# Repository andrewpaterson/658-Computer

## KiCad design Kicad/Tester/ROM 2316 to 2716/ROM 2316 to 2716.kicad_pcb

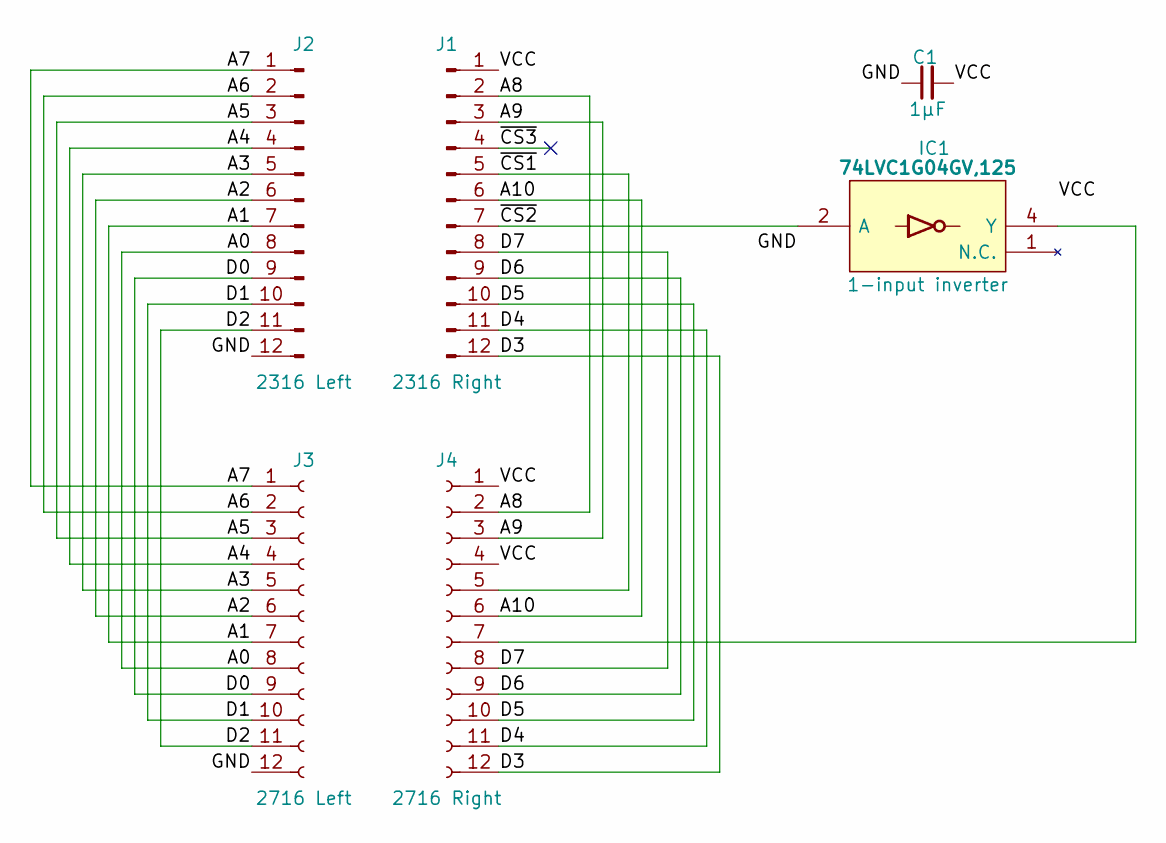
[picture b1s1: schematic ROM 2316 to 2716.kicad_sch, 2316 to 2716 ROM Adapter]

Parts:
C1: 1μF; C_0805
IC1: 74LVC1G04GV,125; SOT95P275X110-5N; Manufacturer_Part_Number 74LVC1G04GV,125; Mouser Part Number 771-74LVC1G04GV
J1: 2316 Right; Pin_1x12_P2.54mm_Vertical
J2: 2316 Left; Pin_1x12_P2.54mm_Vertical
J3: 2716 Left; Pin_1x12_P2.54mm_Vertical
J4: 2716 Right; Pin_1x12_P2.54mm_Vertical

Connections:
/A0: J2.8, J3.8
/A1: J2.7, J3.7
/A2: J2.6, J3.6
/A3: J2.5, J3.5
/A4: J2.4, J3.4
/A5: J2.3, J3.3
/A6: J2.2, J3.2
/A7: J2.1, J3.1
/A8: J1.2, J4.2
/A9: J1.3, J4.3
/A10: J1.6, J4.6
/D0: J2.9, J3.9
/D1: J2.10, J3.10
/D2: J2.11, J3.11
/D3: J1.12, J4.12
/D4: J1.11, J4.11
/D5: J1.10, J4.10
/D6: J1.9, J4.9
/D7: J1.8, J4.8
/GND: C1.1, IC1.3 (GND), J2.12, J3.12
/VCC: C1.2, IC1.5 (3V), J1.1, J4.1, J4.4
/~CS1: J1.5, J4.5
/~CS2: IC1.2 (A), J1.7
/~CS3: J1.4
unnamed: IC1.4 (Y), J4.7

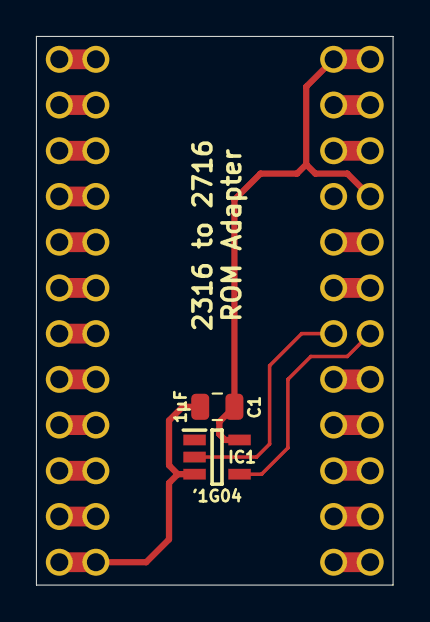
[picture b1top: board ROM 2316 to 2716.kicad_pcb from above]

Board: 2 copper layers, 19.8 x 30.5 mm, 6 parts (0 on the bottom side), 24 nets.

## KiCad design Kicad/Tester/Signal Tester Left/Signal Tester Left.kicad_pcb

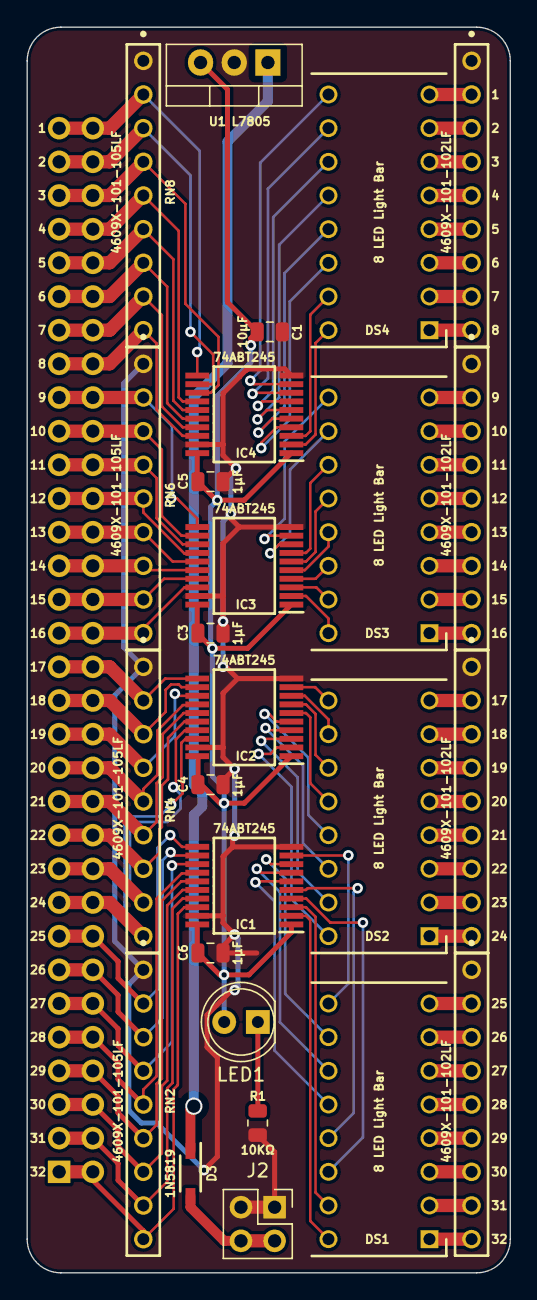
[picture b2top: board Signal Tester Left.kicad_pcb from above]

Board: 2 copper layers, 36.4 x 94.0 mm, 27 parts (1 on the bottom side), 101 nets.

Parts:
C1: 10µF; C_0805
C3, C4, C5, C6: 1μF; C_0805
D3: 1N5819HW-7-F; SOD3716X145N
DS1, DS2, DS3, DS4: 8 LED Light Bar; DIP8LEDBAR
IC1, IC2, IC3, IC4: SN74ABT245BDBR; SOP65P780X200-20N
J2: Conn_02x02_Odd_Even; PinSocket_2x02_P2.54mm_Vertical
J3: Conn_02x32_Odd_Even; PinHeader_2x32_P2.54mm_Vertical
LED1: LED_Small_Filled; LED_D5.0mm
R1: 10KΩ; R_0805
RN1, RN3, RN5, RN7: 4609X-101-102LF; 4609X
RN2, RN4, RN6, RN8: 4609X-101-105LF; 4609X
U1: L7805; TO-220-3_Vertical

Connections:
/5V: C1.1, C3.2, C4.2, C5.2, C6.2, IC1.1 (DIR), IC1.20 (5V), IC2.1 (DIR), IC2.20 (5V), IC3.1 (DIR), IC3.20 (5V), IC4.1 (DIR), IC4.20 (5V), LED1.2 (A), U1.3 (OUT)
/12V Forward: D3.1, U1.1 (IN)
/D0: IC1.18 (B0), J3.1, J3.2, RN2.9 (R8)
/D1: IC1.17 (B1), J3.3, J3.4, RN2.8 (R7)
/D2: IC1.16 (B2), J3.5, J3.6, RN2.7 (R6)
/D3: IC1.15 (B3), J3.7, J3.8, RN2.6 (R5)
/D4: IC1.14 (B4), J3.9, J3.10, RN2.5 (R4)
/D5: IC1.13 (B5), J3.11, J3.12, RN2.4 (R3)
/D6: IC1.12 (B6), J3.13, J3.14, RN2.3 (R2)
/D7: IC1.11 (B7), J3.15, J3.16, RN2.2 (R1)
/D8: IC2.18 (B0), J3.17, J3.18, RN4.9 (R8)
/D9: IC2.17 (B1), J3.19, J3.20, RN4.8 (R7)
/D10: IC2.16 (B2), J3.21, J3.22, RN4.7 (R6)
/D11: IC2.15 (B3), J3.23, J3.24, RN4.6 (R5)
/D12: IC2.14 (B4), J3.25, J3.26, RN4.5 (R4)
/D13: IC2.13 (B5), J3.27, J3.28, RN4.4 (R3)
/D14: IC2.12 (B6), J3.29, J3.30, RN4.3 (R2)
/D15: IC2.11 (B7), J3.31, J3.32, RN4.2 (R1)
/D16: IC3.18 (B0), J3.33, J3.34, RN6.9 (R8)
/D17: IC3.17 (B1), J3.35, J3.36, RN6.8 (R7)
/D18: IC3.16 (B2), J3.37, J3.38, RN6.7 (R6)
/D19: IC3.15 (B3), J3.39, J3.40, RN6.6 (R5)
/D20: IC3.14 (B4), J3.41, J3.42, RN6.5 (R4)
/D21: IC3.13 (B5), J3.43, J3.44, RN6.4 (R3)
/D22: IC3.12 (B6), J3.45, J3.46, RN6.3 (R2)
/D23: IC3.11 (B7), J3.47, J3.48, RN6.2 (R1)
/D24: IC4.18 (B0), J3.49, J3.50, RN8.9 (R8)
/D25: IC4.17 (B1), J3.51, J3.52, RN8.8 (R7)
/D26: IC4.16 (B2), J3.53, J3.54, RN8.7 (R6)
/D27: IC4.15 (B3), J3.55, J3.56, RN8.6 (R5)
/D28: IC4.14 (B4), J3.57, J3.58, RN8.5 (R4)
/D29: IC4.13 (B5), J3.59, J3.60, RN8.4 (R3)
/D30: IC4.12 (B6), J3.61, J3.62, RN8.3 (R2)
/D31: IC4.11 (B7), J3.63, J3.64, RN8.2 (R1)
/GND: C1.2, C3.1, C4.1, C5.1, C6.1, IC1.10 (GND), IC1.19 (~OE), IC2.10 (GND), IC2.19 (~OE), IC3.10 (GND), IC3.19 (~OE), IC4.10 (GND), IC4.19 (~OE), J2.1, J2.2, R1.1, RN1.1 (PC), RN2.1 (PC), RN3.1 (PC), RN4.1 (PC), RN5.1 (PC), RN6.1 (PC), RN7.1 (PC), RN8.1 (PC), U1.2 (GND)
unnamed: DS1.1 (ANODE_A), RN1.9 (R8)
unnamed: DS1.2 (ANODE_B), RN1.8 (R7)
unnamed: DS1.3 (ANODE_C), RN1.7 (R6)
unnamed: DS1.4 (ANODE_D), RN1.6 (R5)
unnamed: DS1.5 (ANODE_E), RN1.5 (R4)
unnamed: DS1.6 (ANODE_F), RN1.4 (R3)
unnamed: DS1.7 (ANODE_G), RN1.3 (R2)
unnamed: DS1.8 (ANODE_H), RN1.2 (R1)
unnamed: DS1.16 (CATHODE_A), IC1.2 (A0)
unnamed: DS1.15 (CATHODE_B), IC1.3 (A1)
unnamed: DS1.14 (CATHODE_C), IC1.4 (A2)
unnamed: DS1.13 (CATHODE_D), IC1.5 (A3)
unnamed: DS1.12 (CATHODE_E), IC1.6 (A4)
unnamed: DS1.11 (CATHODE_F), IC1.7 (A5)
unnamed: DS1.10 (CATHODE_G), IC1.8 (A6)
unnamed: DS1.9 (CATHODE_H), IC1.9 (A7)
unnamed: DS2.1 (ANODE_A), RN3.9 (R8)
unnamed: DS2.2 (ANODE_B), RN3.8 (R7)
unnamed: DS2.3 (ANODE_C), RN3.7 (R6)
unnamed: DS2.4 (ANODE_D), RN3.6 (R5)
unnamed: DS2.5 (ANODE_E), RN3.5 (R4)
unnamed: DS2.6 (ANODE_F), RN3.4 (R3)
unnamed: DS2.7 (ANODE_G), RN3.3 (R2)
unnamed: DS2.8 (ANODE_H), RN3.2 (R1)
unnamed: DS2.16 (CATHODE_A), IC2.2 (A0)
unnamed: DS2.15 (CATHODE_B), IC2.3 (A1)
unnamed: DS2.14 (CATHODE_C), IC2.4 (A2)
unnamed: DS2.13 (CATHODE_D), IC2.5 (A3)
unnamed: DS2.12 (CATHODE_E), IC2.6 (A4)
unnamed: DS2.11 (CATHODE_F), IC2.7 (A5)
unnamed: DS2.10 (CATHODE_G), IC2.8 (A6)
unnamed: DS2.9 (CATHODE_H), IC2.9 (A7)
unnamed: DS3.1 (ANODE_A), RN5.9 (R8)
unnamed: DS3.2 (ANODE_B), RN5.8 (R7)
unnamed: DS3.3 (ANODE_C), RN5.7 (R6)
unnamed: DS3.4 (ANODE_D), RN5.6 (R5)
unnamed: DS3.5 (ANODE_E), RN5.5 (R4)
unnamed: DS3.6 (ANODE_F), RN5.4 (R3)
unnamed: DS3.7 (ANODE_G), RN5.3 (R2)
unnamed: DS3.8 (ANODE_H), RN5.2 (R1)
unnamed: DS3.16 (CATHODE_A), IC3.2 (A0)
unnamed: DS3.15 (CATHODE_B), IC3.3 (A1)
unnamed: DS3.14 (CATHODE_C), IC3.4 (A2)
unnamed: DS3.13 (CATHODE_D), IC3.5 (A3)
unnamed: DS3.12 (CATHODE_E), IC3.6 (A4)
unnamed: DS3.11 (CATHODE_F), IC3.7 (A5)
unnamed: DS3.10 (CATHODE_G), IC3.8 (A6)
unnamed: DS3.9 (CATHODE_H), IC3.9 (A7)
unnamed: DS4.1 (ANODE_A), RN7.9 (R8)
unnamed: DS4.2 (ANODE_B), RN7.8 (R7)
unnamed: DS4.3 (ANODE_C), RN7.7 (R6)
unnamed: DS4.4 (ANODE_D), RN7.6 (R5)
unnamed: DS4.5 (ANODE_E), RN7.5 (R4)
unnamed: DS4.6 (ANODE_F), RN7.4 (R3)
unnamed: DS4.7 (ANODE_G), RN7.3 (R2)
unnamed: DS4.8 (ANODE_H), RN7.2 (R1)
unnamed: DS4.16 (CATHODE_A), IC4.2 (A0)
unnamed: DS4.15 (CATHODE_B), IC4.3 (A1)
unnamed: DS4.14 (CATHODE_C), IC4.4 (A2)
unnamed: DS4.13 (CATHODE_D), IC4.5 (A3)
unnamed: DS4.12 (CATHODE_E), IC4.6 (A4)
unnamed: DS4.11 (CATHODE_F), IC4.7 (A5)
unnamed: DS4.10 (CATHODE_G), IC4.8 (A6)
unnamed: DS4.9 (CATHODE_H), IC4.9 (A7)
unnamed: D3.2, J2.3, J2.4
unnamed: LED1.1 (K), R1.2

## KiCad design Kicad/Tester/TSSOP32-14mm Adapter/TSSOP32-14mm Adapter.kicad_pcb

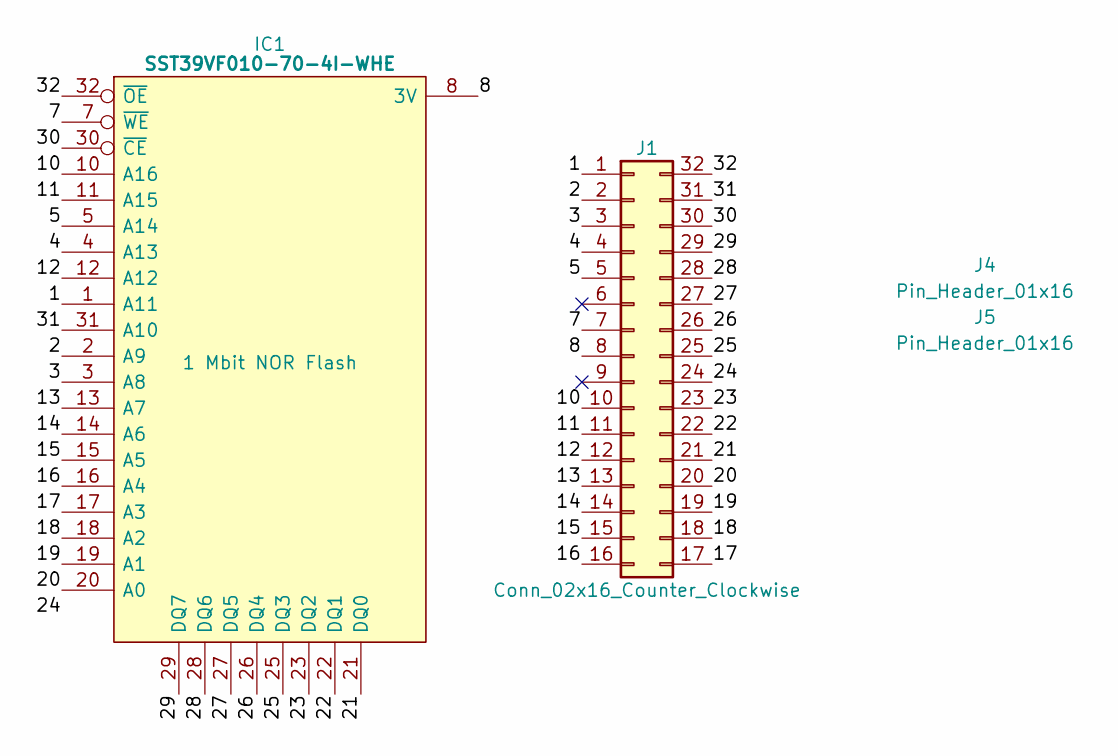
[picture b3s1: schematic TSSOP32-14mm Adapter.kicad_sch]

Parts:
IC1: SST39VF010-70-4I-WHE; SOP50P1400X120-32N; Manufacturer_Part_Number SST39VF010-70-4I-WHE-T; Mouser Part Number 579-39VF0107IWHET
J1: Conn_02x16_Counter_Clockwise; DIP-32_W15.24mm_Socket
J4, J5: Pin_Header_01x16; PinHeader_1x16_P2.54mm_Vertical

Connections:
/1: IC1.1 (A11), J1.1
/2: IC1.2 (A9), J1.2
/3: IC1.3 (A8), J1.3
/4: IC1.4 (A13), J1.4
/5: IC1.5 (A14), J1.5
/7: IC1.7 (~WE), J1.7
/8: IC1.8 (3V), J1.8
/10: IC1.10 (A16), J1.10
/11: IC1.11 (A15), J1.11
/12: IC1.12 (A12), J1.12
/13: IC1.13 (A7), J1.13
/14: IC1.14 (A6), J1.14
/15: IC1.15 (A5), J1.15
/16: IC1.16 (A4), J1.16
/17: IC1.17 (A3), J1.17
/18: IC1.18 (A2), J1.18
/19: IC1.19 (A1), J1.19
/20: IC1.20 (A0), J1.20
/21: IC1.21 (DQ0), J1.21
/22: IC1.22 (DQ1), J1.22
/23: IC1.23 (DQ2), J1.23
/24: IC1.24 (GND), J1.24
/25: IC1.25 (DQ3), J1.25
/26: IC1.26 (DQ4), J1.26
/27: IC1.27 (DQ5), J1.27
/28: IC1.28 (DQ6), J1.28
/29: IC1.29 (DQ7), J1.29
/30: IC1.30 (~CE), J1.30
/31: IC1.31 (A10), J1.31
/32: IC1.32 (~OE), J1.32

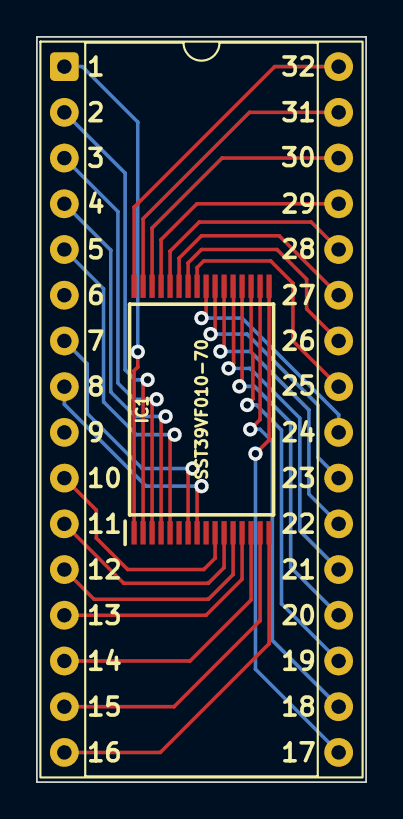
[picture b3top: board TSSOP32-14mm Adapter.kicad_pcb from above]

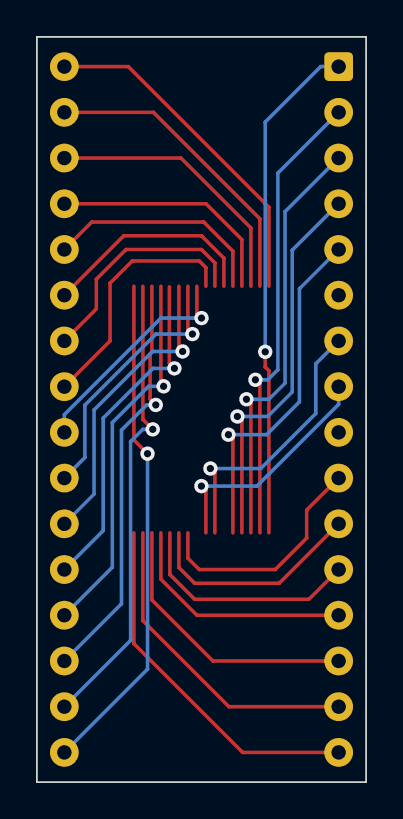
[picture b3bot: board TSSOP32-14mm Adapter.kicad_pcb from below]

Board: 2 copper layers, 18.3 x 41.4 mm, 4 parts (2 on the bottom side), 30 nets.

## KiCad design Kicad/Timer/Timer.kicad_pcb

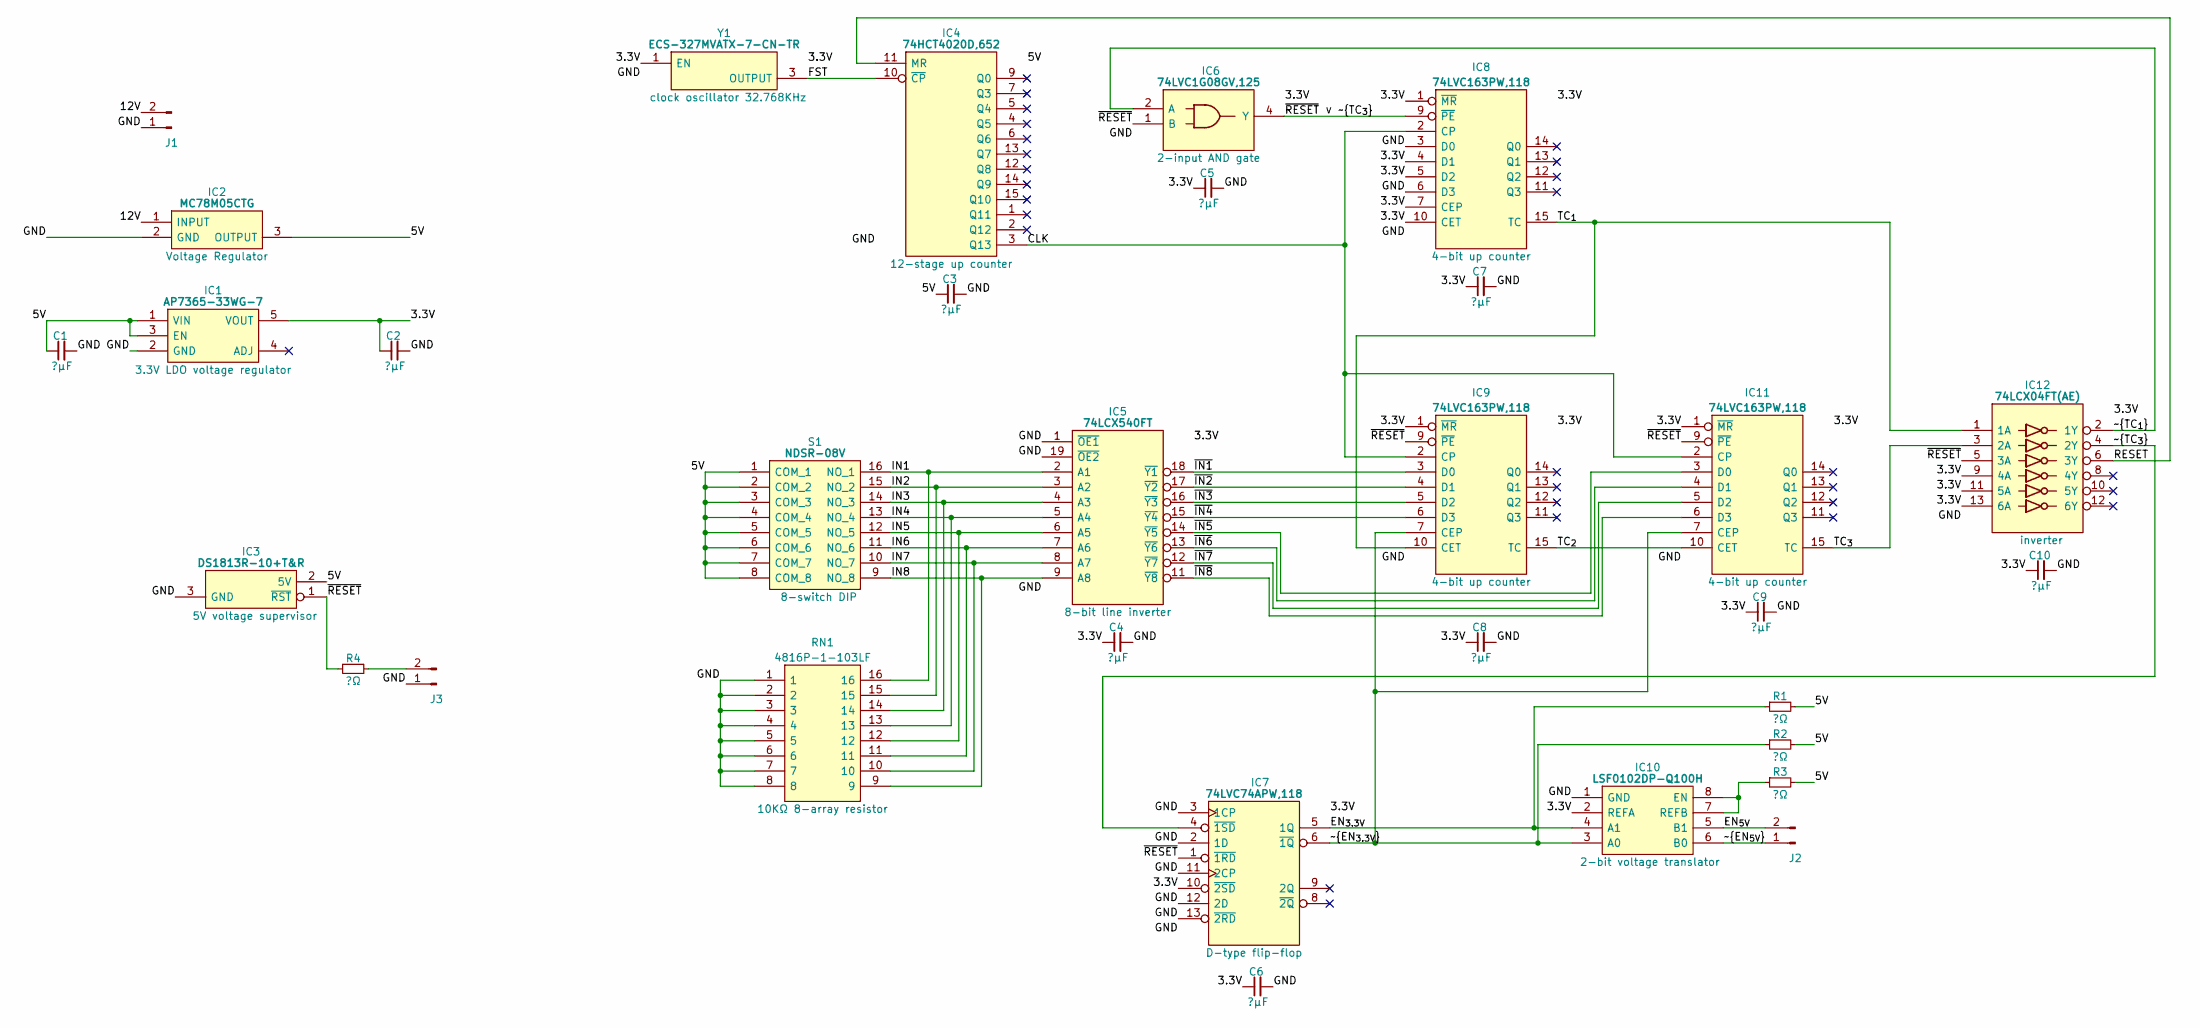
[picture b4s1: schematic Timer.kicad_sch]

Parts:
C1, C2, C3, C4, C5, C6, C7, C8, C9, C10: C_0805
IC1: AP7365-33WG-7; SOT95P285X130-5N; Manufacturer_Part_Number AP7365-33WG-7; Mouser Part Number 621-AP7365-33WG-7
IC2: MC78M05CTG; TO254P482X997X2018-3P; Manufacturer_Part_Number MC78M05CTG; Mouser Part Number 863-MC78M05CTG
IC3: DS1813R-10+T&R; SOT95P237X112-3N; Mouser Part Number 700-DS1813R-10T&R
IC4: 74HCT4020D,652; 74HCT4020D652; Manufacturer_Part_Number 74HCT4020D,652; Mouser Part Number 771-74HCT4020D
IC5: 74LCX540FT; SOP65P640X120-20N; Manufacturer_Part_Number 74LCX540FT; Mouser Part Number 757-74LCX540FT
IC6: 74LVC1G08GV,125; SOT95P275X110-5N; Manufacturer_Part_Number 74LVC1G08GV,125; Mouser Part Number 771-74LVC1G08GV
IC7: 74LVC74APW,118; SOP65P640X110-14N; Mouser Part Number 771-74LVC74APW-T
IC8, IC9, IC11: 74LVC163PW,118; SOP65P640X110-16N; Mouser Part Number 771-74LVC163PW-T
IC10: LSF0102DP-Q100H; SOP65P400X110-8N; Manufacturer_Part_Number LSF0102DP-Q100H; Mouser Part Number 771-LSF0102DP-Q100H
IC12: 74LCX04FT(AE); SOP65P640X120-14N; Mouser Part Number 757-74LCX04FTAE
J1, J2, J3: Conn_01x02_Male
R1, R2, R3, R4: R_0805
RN1: 4816P-1-103LF; SOIC127P762X240-16N; Manufacturer_Part_Number 4816P-1-103LF; Mouser Part Number 652-4816P-1LF-10K
S1: NDSR-08V; DIPS762W77P254L2168H585Q16N; Manufacturer_Part_Number NDSR-08-V
Y1: ECS-327MVATX-7-CN-TR; ECS327MVATX7CNTR; Manufacturer_Part_Number ECS-327MVATX-7-CN-TR; Mouser Part Number 520-327MVATX-7-CNT

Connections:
/3.3V: C2.1, C4.1, C5.1, C6.1, C7.1, C8.1, C9.1, C10.1, IC1.5 (VOUT), IC5.20 (3V), IC6.5 (3V), IC7.10 (~2SD), IC7.14 (3V), IC8.1 (~MR), IC8.4 (D1), IC8.5 (D2), IC8.7 (CEP), IC8.10 (CET), IC8.16 (3V), IC9.1 (~MR), IC9.16 (3V), IC10.2 (REFA), IC11.1 (~MR), IC11.16 (3V), IC12.9 (4A), IC12.11 (5A), IC12.13 (6A), IC12.14 (3V), Y1.1 (EN), Y1.4 (3V)
/5V: C1.1, C3.1, IC1.1 (VIN), IC1.3 (EN), IC2.3 (OUTPUT), IC3.2 (5V), IC4.16 (5V), R1.2, R2.2, R3.2, S1.1 (COM_1), S1.2 (COM_2), S1.3 (COM_3), S1.4 (COM_4), S1.5 (COM_5), S1.6 (COM_6), S1.7 (COM_7), S1.8 (COM_8)
/12V: IC2.1 (INPUT), J1.2
/CLK: IC4.3 (Q13), IC8.2 (CP), IC9.2 (CP), IC11.2 (CP)
/EN_{3.3V}: IC7.5 (1Q), IC10.4 (A1), R1.1
/EN_{5V}: IC10.5 (B1), J2.2
/FST: IC4.10 (~CP), Y1.3 (OUTPUT)
/GND: C1.2, C2.2, C3.2, C4.2, C5.2, C6.2, C7.2, C8.2, C9.2, C10.2, IC1.2 (GND), IC2.2 (GND), IC3.3 (GND), IC4.8 (GND), IC5.1 (~OE1), IC5.10 (GND), IC5.19 (~OE2), IC6.3 (GND), IC7.2 (1D), IC7.3 (1CP), IC7.7 (GND), IC7.11 (2CP), IC7.12 (2D), IC7.13 (~2RD), IC8.3 (D0), IC8.6 (D3), IC8.8 (GND), IC9.8 (GND), IC10.1 (GND), IC11.8 (GND), IC12.7 (GND), J1.1, J3.1, RN1.1, RN1.2, RN1.3, RN1.4, RN1.5, RN1.6, RN1.7, RN1.8, Y1.2 (GND)
/IN1: IC5.2 (A1), RN1.16, S1.16 (NO_1)
/IN2: IC5.3 (A2), RN1.15, S1.15 (NO_2)
/IN3: IC5.4 (A3), RN1.14, S1.14 (NO_3)
/IN4: IC5.5 (A4), RN1.13, S1.13 (NO_4)
/IN5: IC5.6 (A5), RN1.12, S1.12 (NO_5)
/IN6: IC5.7 (A6), RN1.11, S1.11 (NO_6)
/IN7: IC5.8 (A7), RN1.10, S1.10 (NO_7)
/IN8: IC5.9 (A8), RN1.9, S1.9 (NO_8)
/RESET: IC4.11 (MR), IC12.6 (3Y)
/TC_{1}: IC8.15 (TC), IC9.10 (CET), IC12.1 (1A)
/TC_{2}: IC9.15 (TC), IC11.10 (CET)
/TC_{3}: IC11.15 (TC), IC12.3 (2A)
/~EN_{3.3V}: IC7.6 (~1Q), IC9.7 (CEP), IC10.3 (A0), IC11.7 (CEP), R2.1
/~EN_{5V}: IC10.6 (B0), J2.1
/~IN1: IC5.18 (~Y1), IC9.3 (D0)
/~IN2: IC5.17 (~Y2), IC9.4 (D1)
/~IN3: IC5.16 (~Y3), IC9.5 (D2)
/~IN4: IC5.15 (~Y4), IC9.6 (D3)
/~IN5: IC5.14 (~Y5), IC11.3 (D0)
/~IN6: IC5.13 (~Y6), IC11.4 (D1)
/~IN7: IC5.12 (~Y7), IC11.5 (D2)
/~IN8: IC5.11 (~Y8), IC11.6 (D3)
/~RESET: IC3.1 (~RST), IC6.1 (B), IC7.1 (~1RD), IC9.9 (~PE), IC11.9 (~PE), IC12.5 (3A), R4.1
/~RESET ∨ ~TC_{3}: IC6.4 (Y), IC8.9 (~PE)
/~TC_{1}: IC6.2 (A), IC12.2 (1Y)
/~TC_{3}: IC7.4 (~1SD), IC12.4 (2Y)
unnamed: IC10.7 (REFB), IC10.8 (EN), R3.1
unnamed: J3.2, R4.2

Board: 2 copper layers, 32 parts (0 on the bottom side), 36 nets, no tracks yet.

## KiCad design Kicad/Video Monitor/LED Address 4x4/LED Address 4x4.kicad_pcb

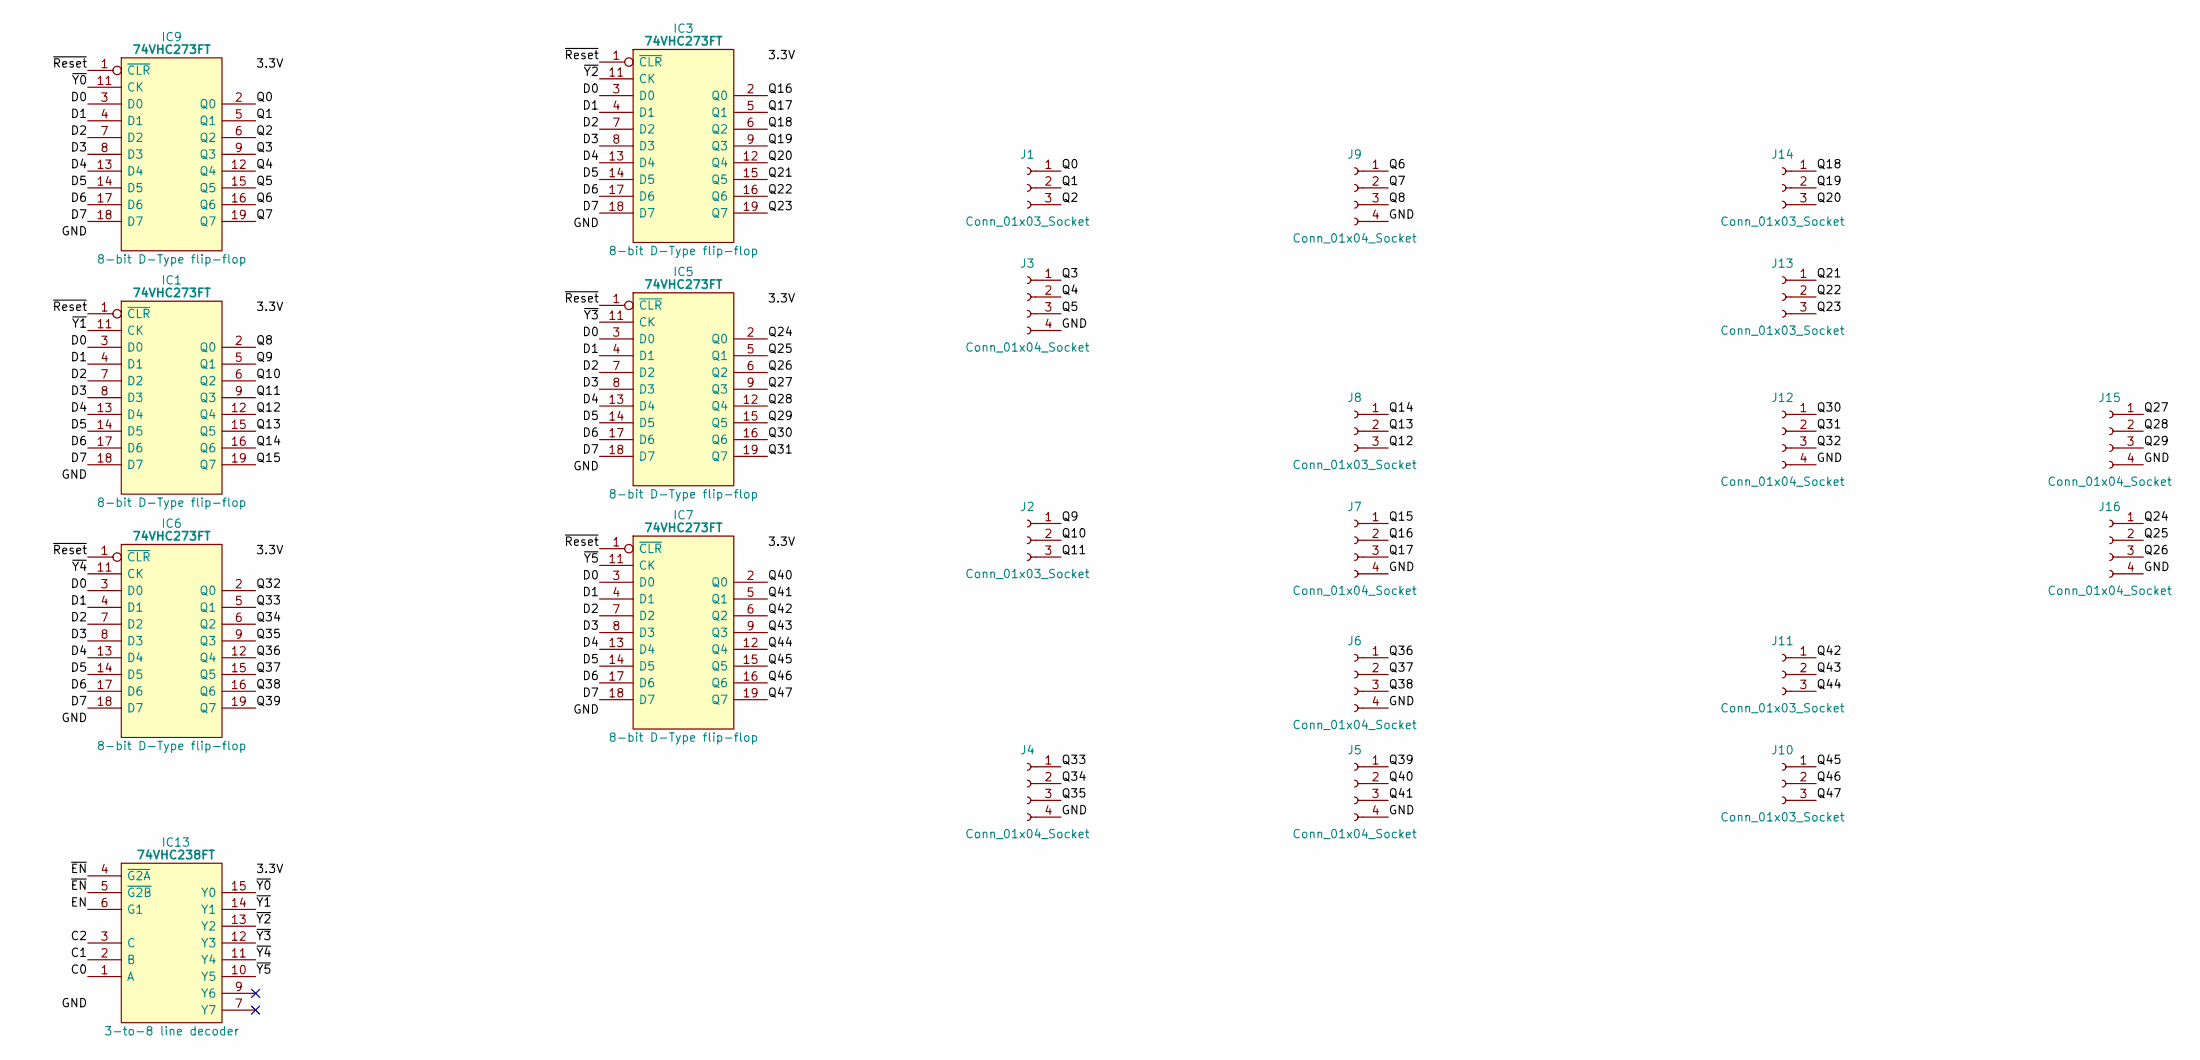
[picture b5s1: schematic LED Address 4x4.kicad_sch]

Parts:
IC1, IC3, IC5, IC6, IC7, IC9: 74VHC273FT; SOP65P640X110-20N; Manufacturer_Part_Number 74VHC273FT
IC13: 74VHC238FT; SOP65P640X120-16N; Mouser Part Number 757-74VHC238FT
J1, J2, J8, J10, J11, J13, J14: Conn_01x03_Socket; LED_Connector_3_SMD
J3, J4, J5, J6, J7, J9, J12, J15, J16: Conn_01x04_Socket; LED_Connector_4_SMD

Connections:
/3.3V: IC1.20 (5V), IC3.20 (5V), IC5.20 (5V), IC6.20 (5V), IC7.20 (5V), IC9.20 (5V), IC13.16 (5V)
/C0: IC13.1 (A)
/C1: IC13.2 (B)
/C2: IC13.3 (C)
/D0: IC1.3 (D0), IC3.3 (D0), IC5.3 (D0), IC6.3 (D0), IC7.3 (D0), IC9.3 (D0)
/D1: IC1.4 (D1), IC3.4 (D1), IC5.4 (D1), IC6.4 (D1), IC7.4 (D1), IC9.4 (D1)
/D2: IC1.7 (D2), IC3.7 (D2), IC5.7 (D2), IC6.7 (D2), IC7.7 (D2), IC9.7 (D2)
/D3: IC1.8 (D3), IC3.8 (D3), IC5.8 (D3), IC6.8 (D3), IC7.8 (D3), IC9.8 (D3)
/D4: IC1.13 (D4), IC3.13 (D4), IC5.13 (D4), IC6.13 (D4), IC7.13 (D4), IC9.13 (D4)
/D5: IC1.14 (D5), IC3.14 (D5), IC5.14 (D5), IC6.14 (D5), IC7.14 (D5), IC9.14 (D5)
/D6: IC1.17 (D6), IC3.17 (D6), IC5.17 (D6), IC6.17 (D6), IC7.17 (D6), IC9.17 (D6)
/D7: IC1.18 (D7), IC3.18 (D7), IC5.18 (D7), IC6.18 (D7), IC7.18 (D7), IC9.18 (D7)
/EN: IC13.6 (G1)
/GND: IC1.10 (GND), IC3.10 (GND), IC5.10 (GND), IC6.10 (GND), IC7.10 (GND), IC9.10 (GND), IC13.8 (GND), J3.4, J4.4, J5.4, J6.4, J7.4, J9.4, J12.4, J15.4, J16.4
/Q0: IC9.2 (Q0), J1.1
/Q1: IC9.5 (Q1), J1.2
/Q2: IC9.6 (Q2), J1.3
/Q3: IC9.9 (Q3), J3.1
/Q4: IC9.12 (Q4), J3.2
/Q5: IC9.15 (Q5), J3.3
/Q6: IC9.16 (Q6), J9.1
/Q7: IC9.19 (Q7), J9.2
/Q8: IC1.2 (Q0), J9.3
/Q9: IC1.5 (Q1), J2.1
/Q10: IC1.6 (Q2), J2.2
/Q11: IC1.9 (Q3), J2.3
/Q12: IC1.12 (Q4), J8.3
/Q13: IC1.15 (Q5), J8.2
/Q14: IC1.16 (Q6), J8.1
/Q15: IC1.19 (Q7), J7.1
/Q16: IC3.2 (Q0), J7.2
/Q17: IC3.5 (Q1), J7.3
/Q18: IC3.6 (Q2), J14.1
/Q19: IC3.9 (Q3), J14.2
/Q20: IC3.12 (Q4), J14.3
/Q21: IC3.15 (Q5), J13.1
/Q22: IC3.16 (Q6), J13.2
/Q23: IC3.19 (Q7), J13.3
/Q24: IC5.2 (Q0), J16.1
/Q25: IC5.5 (Q1), J16.2
/Q26: IC5.6 (Q2), J16.3
/Q27: IC5.9 (Q3), J15.1
/Q28: IC5.12 (Q4), J15.2
/Q29: IC5.15 (Q5), J15.3
/Q30: IC5.16 (Q6), J12.1
/Q31: IC5.19 (Q7), J12.2
/Q32: IC6.2 (Q0), J12.3
/Q33: IC6.5 (Q1), J4.1
/Q34: IC6.6 (Q2), J4.2
/Q35: IC6.9 (Q3), J4.3
/Q36: IC6.12 (Q4), J6.1
/Q37: IC6.15 (Q5), J6.2
/Q38: IC6.16 (Q6), J6.3
/Q39: IC6.19 (Q7), J5.1
/Q40: IC7.2 (Q0), J5.2
/Q41: IC7.5 (Q1), J5.3
/Q42: IC7.6 (Q2), J11.1
/Q43: IC7.9 (Q3), J11.2
/Q44: IC7.12 (Q4), J11.3
/Q45: IC7.15 (Q5), J10.1
/Q46: IC7.16 (Q6), J10.2
/Q47: IC7.19 (Q7), J10.3
/~EN: IC13.4 (~G2A), IC13.5 (~G2B)
/~Reset: IC1.1 (~CLR), IC3.1 (~CLR), IC5.1 (~CLR), IC6.1 (~CLR), IC7.1 (~CLR), IC9.1 (~CLR)
/~Y0: IC9.11 (CK), IC13.15 (Y0)
/~Y1: IC1.11 (CK), IC13.14 (Y1)
/~Y2: IC3.11 (CK), IC13.13 (Y2)
/~Y3: IC5.11 (CK), IC13.12 (Y3)
/~Y4: IC6.11 (CK), IC13.11 (Y4)
/~Y5: IC7.11 (CK), IC13.10 (Y5)

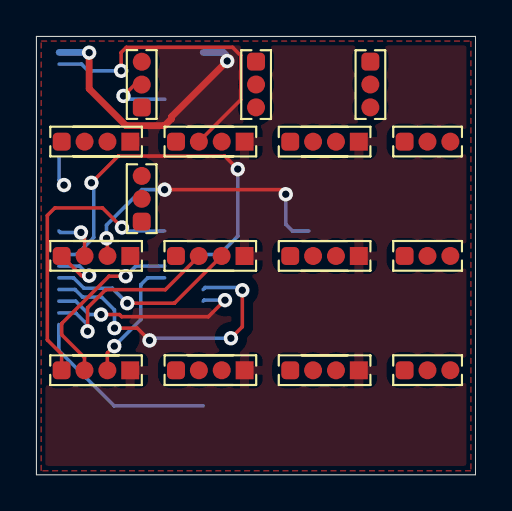
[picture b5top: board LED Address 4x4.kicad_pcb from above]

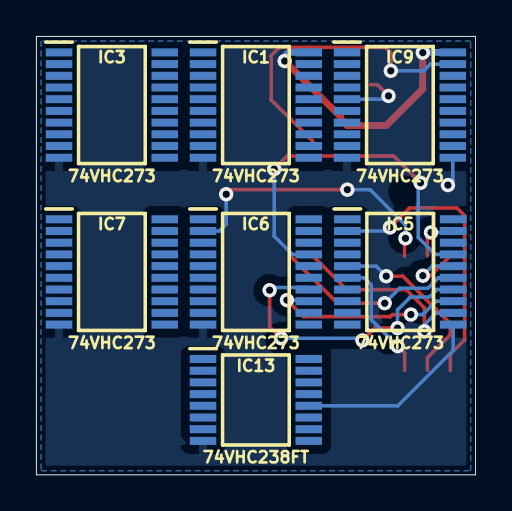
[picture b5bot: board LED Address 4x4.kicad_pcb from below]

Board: 2 copper layers, 24.4 x 24.4 mm, 23 parts (7 on the bottom side), 66 nets.

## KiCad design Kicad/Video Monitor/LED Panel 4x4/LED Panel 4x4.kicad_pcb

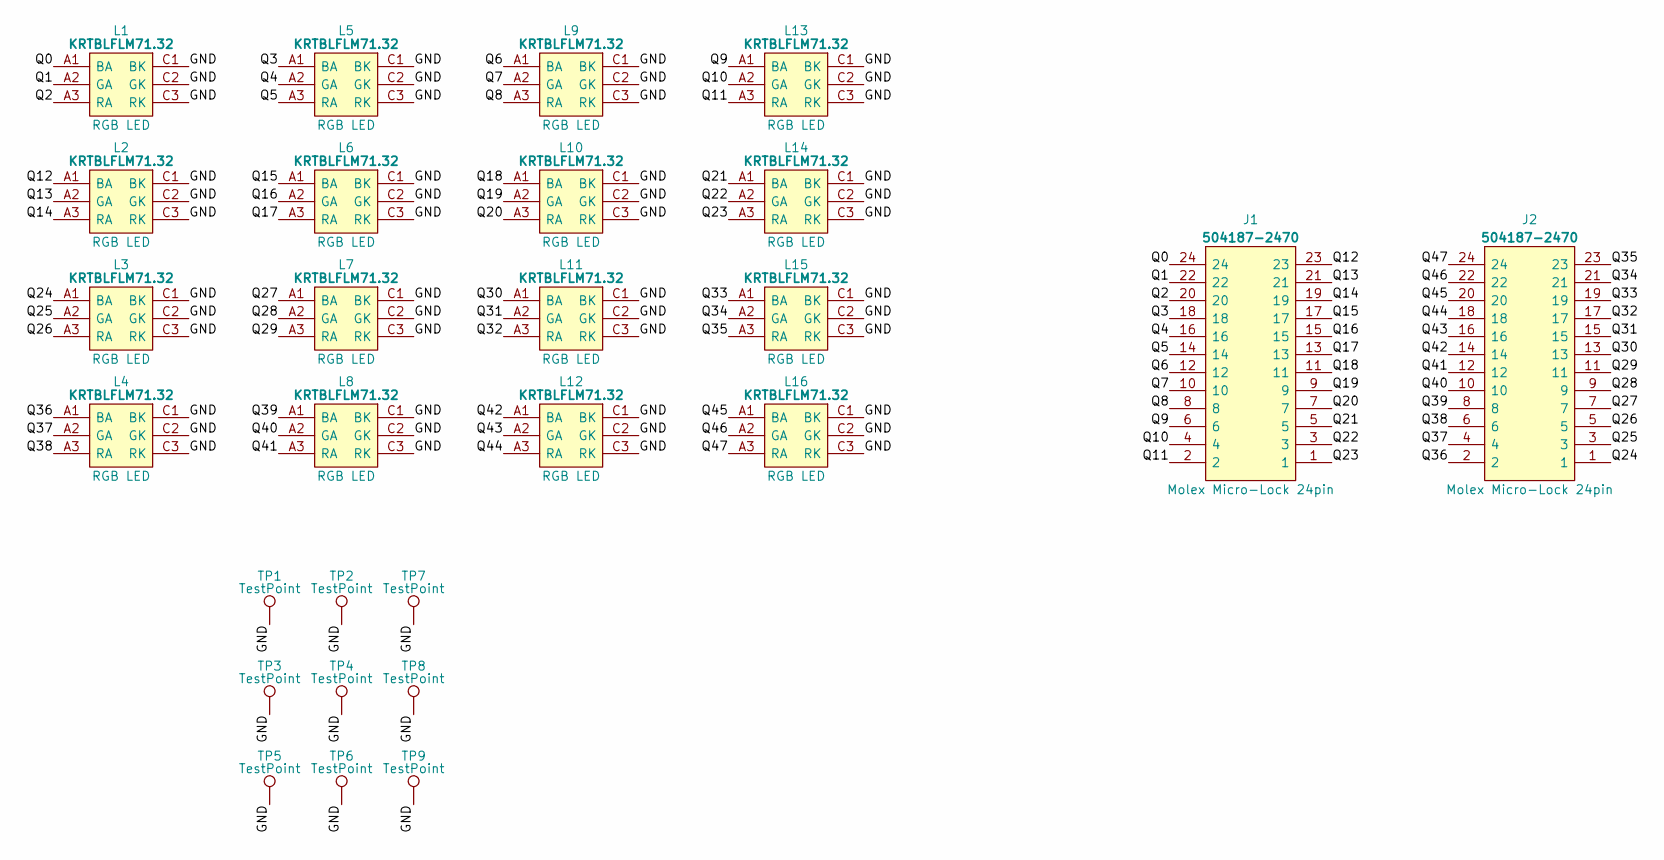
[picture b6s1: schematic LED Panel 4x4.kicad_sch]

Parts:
J1, J2: 504187-2470; 5041872470; Manufacturer_Part_Number 504187-2470; Mouser Part Number 538-504187-2470
L1, L2, L3, L4, L5, L6, L7, L8, L9, L10, L11, L12, L13, L14, L15, L16: KRTBLFLM71.32; KRTBLFLM7132TXUYEVVTAUDPRXTUKY; Manufacturer_Part_Number KRTBLFLM71.32-TXUY-EV+VTAU-DP+RXTU-KY
TP1, TP2, TP3, TP4, TP5, TP6, TP7, TP8, TP9: TestPoint; Point_D1.0mm_Drill0.5mm

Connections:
/GND: L1.C1 (BK), L1.C2 (GK), L1.C3 (RK), L2.C1 (BK), L2.C2 (GK), L2.C3 (RK), L3.C1 (BK), L3.C2 (GK), L3.C3 (RK), L4.C1 (BK), L4.C2 (GK), L4.C3 (RK), L5.C1 (BK), L5.C2 (GK), L5.C3 (RK), L6.C1 (BK), L6.C2 (GK), L6.C3 (RK), L7.C1 (BK), L7.C2 (GK), L7.C3 (RK), L8.C1 (BK), L8.C2 (GK), L8.C3 (RK), L9.C1 (BK), L9.C2 (GK), L9.C3 (RK), L10.C1 (BK), L10.C2 (GK), L10.C3 (RK), L11.C1 (BK), L11.C2 (GK), L11.C3 (RK), L12.C1 (BK), L12.C2 (GK), L12.C3 (RK), L13.C1 (BK), L13.C2 (GK), L13.C3 (RK), L14.C1 (BK), L14.C2 (GK), L14.C3 (RK), L15.C1 (BK), L15.C2 (GK), L15.C3 (RK), L16.C1 (BK), L16.C2 (GK), L16.C3 (RK), TP1.1, TP2.1, TP3.1, TP4.1, TP5.1, TP6.1, TP7.1, TP8.1, TP9.1
/Q0: J1.24, L1.A1 (BA)
/Q1: J1.22, L1.A2 (GA)
/Q2: J1.20, L1.A3 (RA)
/Q3: J1.18, L5.A1 (BA)
/Q4: J1.16, L5.A2 (GA)
/Q5: J1.14, L5.A3 (RA)
/Q6: J1.12, L9.A1 (BA)
/Q7: J1.10, L9.A2 (GA)
/Q8: J1.8, L9.A3 (RA)
/Q9: J1.6, L13.A1 (BA)
/Q10: J1.4, L13.A2 (GA)
/Q11: J1.2, L13.A3 (RA)
/Q12: J1.23, L2.A1 (BA)
/Q13: J1.21, L2.A2 (GA)
/Q14: J1.19, L2.A3 (RA)
/Q15: J1.17, L6.A1 (BA)
/Q16: J1.15, L6.A2 (GA)
/Q17: J1.13, L6.A3 (RA)
/Q18: J1.11, L10.A1 (BA)
/Q19: J1.9, L10.A2 (GA)
/Q20: J1.7, L10.A3 (RA)
/Q21: J1.5, L14.A1 (BA)
/Q22: J1.3, L14.A2 (GA)
/Q23: J1.1, L14.A3 (RA)
/Q24: J2.1, L3.A1 (BA)
/Q25: J2.3, L3.A2 (GA)
/Q26: J2.5, L3.A3 (RA)
/Q27: J2.7, L7.A1 (BA)
/Q28: J2.9, L7.A2 (GA)
/Q29: J2.11, L7.A3 (RA)
/Q30: J2.13, L11.A1 (BA)
/Q31: J2.15, L11.A2 (GA)
/Q32: J2.17, L11.A3 (RA)
/Q33: J2.19, L15.A1 (BA)
/Q34: J2.21, L15.A2 (GA)
/Q35: J2.23, L15.A3 (RA)
/Q36: J2.2, L4.A1 (BA)
/Q37: J2.4, L4.A2 (GA)
/Q38: J2.6, L4.A3 (RA)
/Q39: J2.8, L8.A1 (BA)
/Q40: J2.10, L8.A2 (GA)
/Q41: J2.12, L8.A3 (RA)
/Q42: J2.14, L12.A1 (BA)
/Q43: J2.16, L12.A2 (GA)
/Q44: J2.18, L12.A3 (RA)
/Q45: J2.20, L16.A1 (BA)
/Q46: J2.22, L16.A2 (GA)
/Q47: J2.24, L16.A3 (RA)

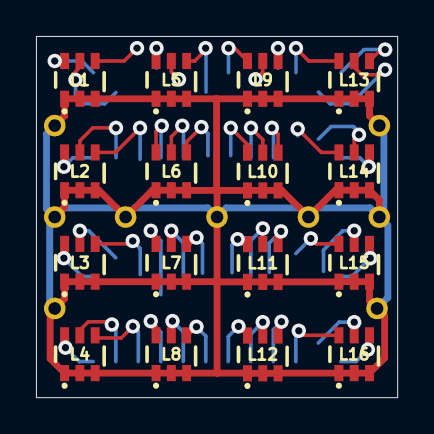
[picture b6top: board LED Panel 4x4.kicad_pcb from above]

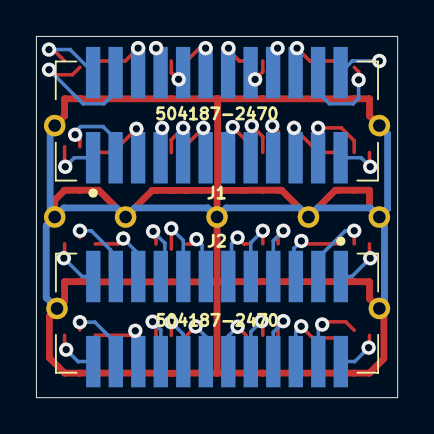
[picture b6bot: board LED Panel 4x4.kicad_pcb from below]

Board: 2 copper layers, 20.1 x 20.1 mm, 27 parts (2 on the bottom side), 49 nets.
